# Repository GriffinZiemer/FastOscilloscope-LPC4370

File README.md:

# FastOscilloscope-LPC4370

Inform others when downloading kiCAD files to work and merge, if multiple people work and merge at the same time, work will be lost... Using MCU as a top hierarchy, implement other blocks within... Powersupply, Analog Front End etc.

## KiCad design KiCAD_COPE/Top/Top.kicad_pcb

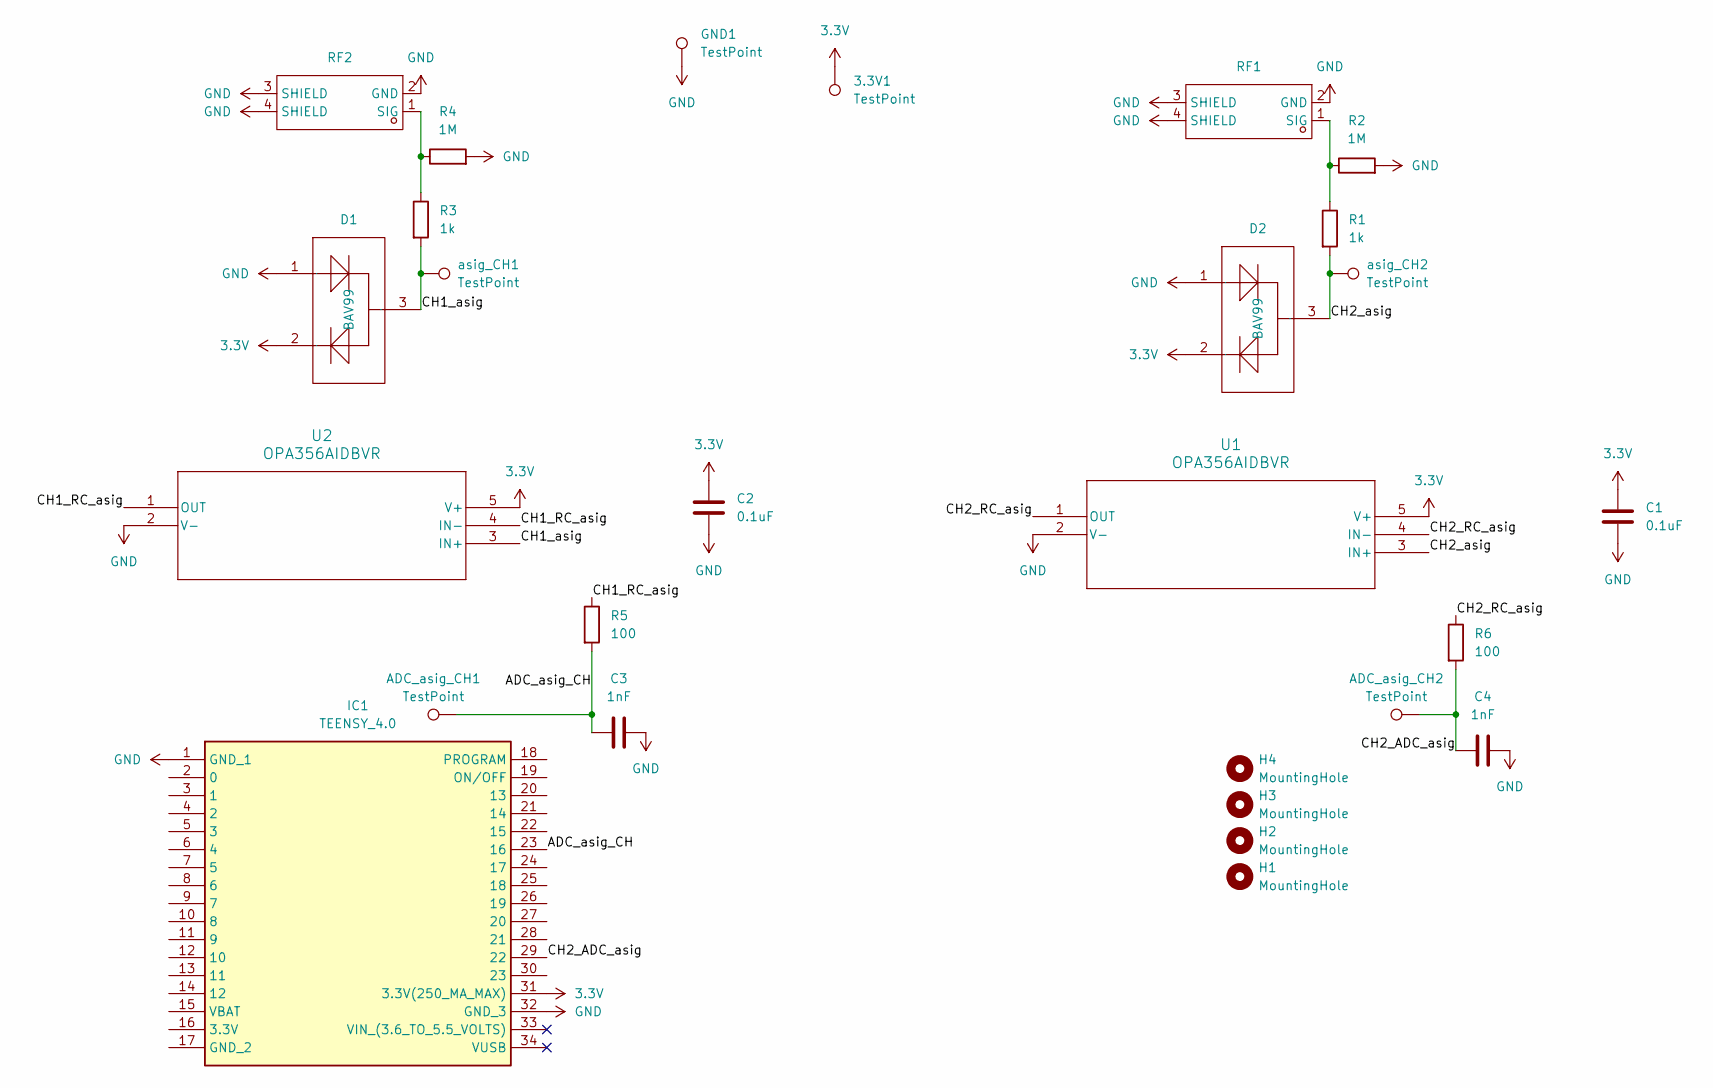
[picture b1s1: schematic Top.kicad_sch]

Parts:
3.3V1: TestPoint; TestPoint_Pad_1.0x1.0mm
ADC_asig_CH1, ADC_asig_CH2: TestPoint; TestPoint_Pad_1.0x1.0mm
C1, C2: 0.1uF; C_0402_1005Metric
C3, C4: 1nF; C_0402_1005Metric
D1, D2: BAV99; SOT-23-3_L2.9-W1.6-P1.90-LS2.8-BR-ESD; Manufacturer Part BAV99,215; LCSC Part Name 100V 215mA
GND1: TestPoint; TestPoint_Pad_1.0x1.0mm
H1, H2, H3, H4: MountingHole; MountingHole_2.2mm_M2
IC1: TEENSY_4.0; TEENSY4.0; Manufacturer_Part_Number TEENSY 4.0
R1, R3: 1k; R_0402_1005Metric
R2, R4: 1M; R_0402_1005Metric
R5, R6: 100; R_0402_1005Metric
RF1, RF2: BNC; BNC Connector 2.0; Manufacturer Part DOSIN-801-0038; LCSC Part Name 3件套 内孔 BNC 弯头
U1, U2: OPA356AIDBVR; DBV5-OPAMP
asig_CH1, asig_CH2: TestPoint; TestPoint_Pad_1.0x1.0mm

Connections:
3.3V: 3.3V1.1 (1_1), C1.1, C2.1, D1.2, D2.2, IC1.31 (3.3V(250_MA_MAX)), U1.5 (V+), U2.5 (V+)
/ADC_asig_CH: ADC_asig_CH1.1 (1_1), C3.1, IC1.23 (16), R5.2
/CH1_RC_asig: R5.1, U2.1 (OUT), U2.4 (IN-)
/CH1_asig: D1.3, R3.2, U2.3 (IN+), asig_CH1.1 (1_1)
/CH2_ADC_asig: ADC_asig_CH2.1 (1_1), C4.1, IC1.29 (22), R6.2
/CH2_RC_asig: R6.1, U1.1 (OUT), U1.4 (IN-)
/CH2_asig: D2.3, R1.2, U1.3 (IN+), asig_CH2.1 (1_1)
GND: C1.2, C2.2, C3.2, C4.2, D1.1, D2.1, GND1.1 (1_1), IC1.1 (GND_1), IC1.32 (GND_3), R2.2, R4.2, RF1.2 (GND), RF1.3 (SHIELD), RF1.4 (SHIELD), RF2.2 (GND), RF2.3 (SHIELD), RF2.4 (SHIELD), U1.2 (V-), U2.2 (V-)
unnamed: R1.1, R2.1, RF1.1 (SIG)
unnamed: R3.1, R4.1, RF2.1 (SIG)

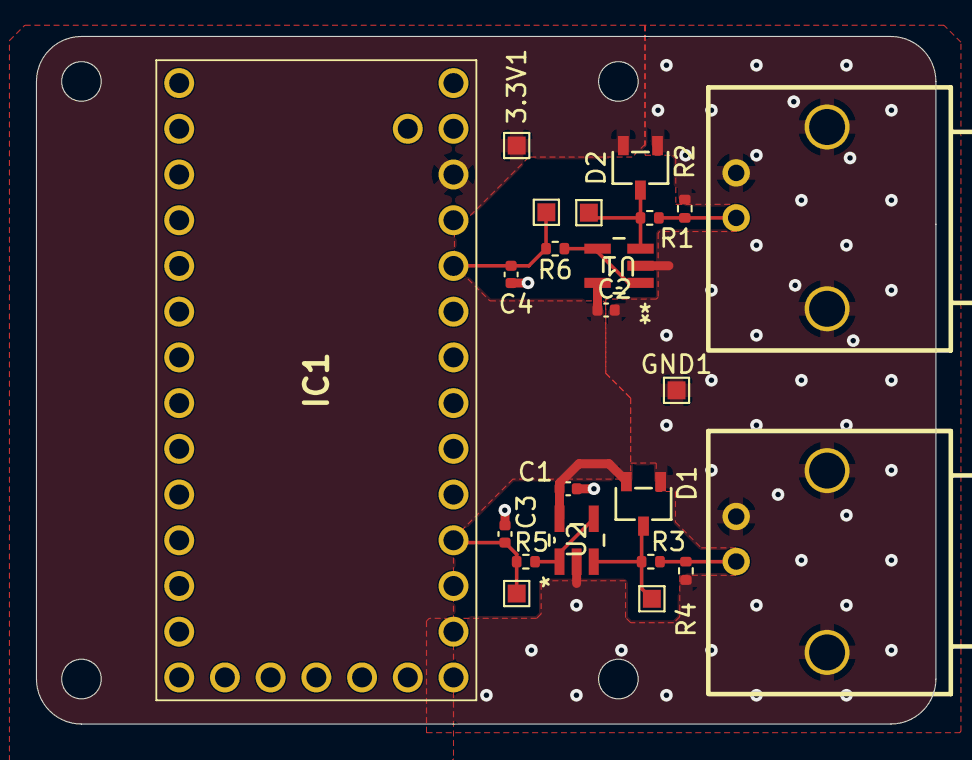
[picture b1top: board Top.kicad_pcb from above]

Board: 2 copper layers, 50.0 x 38.2 mm, 27 parts (0 on the bottom side), 10 nets.

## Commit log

2026-04-15 Create .gitignore
    git ignore for KiCAD files
2026-04-15 Initial commit: LPC4370 MCU board with USB-C and Oscillator libraries
2026-04-15 Update README.md
    info about the kiCAD files.
2026-04-15 Organize: Move hardware files into KiCAD folder
2026-06-06 Fix: Hard reset to working directory state
